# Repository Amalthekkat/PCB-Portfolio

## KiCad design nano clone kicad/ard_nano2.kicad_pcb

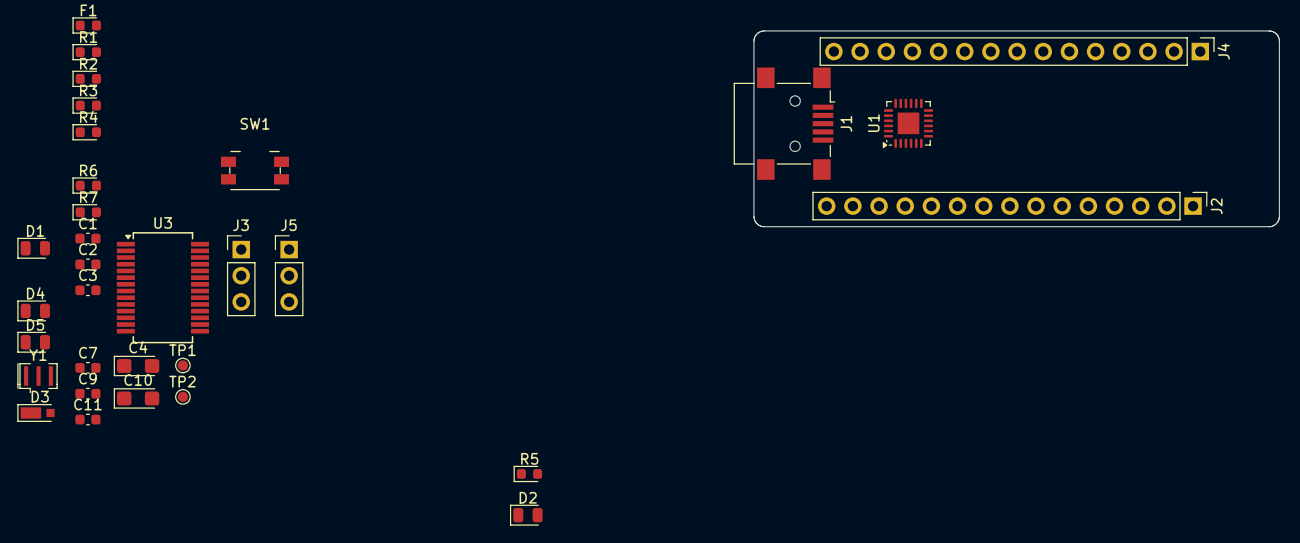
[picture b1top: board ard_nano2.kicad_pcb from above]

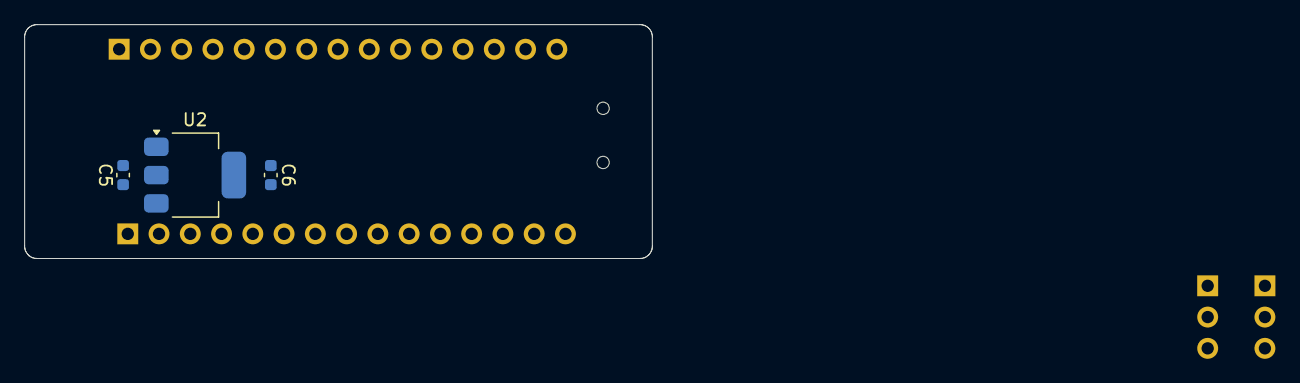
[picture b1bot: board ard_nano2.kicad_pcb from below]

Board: 4 copper layers, 51.0 x 19.0 mm, 35 parts (3 on the bottom side), 40 nets, no tracks yet.

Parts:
C1, C2: 1u; C_0603_1608Metric
C3, C5, C6, C7, C9, C11: 100n; C_0603_1608Metric
C4, C10: 4u7_16V; CP_EIA-3216-10_Kemet-I
D1: YELLOW; LED_0805_2012Metric
D2, D5: GREEN; LED_0805_2012Metric
D3: DIODE; D_MicroSMP_AK
D4: RED; LED_0805_2012Metric
F1: 0603; D_0603_1608Metric
J1: USB_B_Mini; USB_Mini-B_Lumberg_2486_01_Horizontal
J2, J4: PinHeader_1x15_P2.54mm_Vertical
J3: ICSP; PinHeader_1x03_P2.54mm_Vertical
J5: PinHeader_1x03_P2.54mm_Vertical
R1, R2, R3, R4, R5, R6, R7: 1K; D_0603_1608Metric
SW1: Panasonic_EVQPUK_EVQPUB
TP1, TP2: TestPoint_Pad_D1.0mm
U1: ATmega328-M; HVQFN-24-1EP_4x4mm_P0.5mm_EP2.1x2.1mm
U2: LM1117MP-5.0; SOT-223-3_TabPin2
U3: FT232RL; SSOP-28_5.3x10.2mm_P0.65mm
Y1: 16MHz; Resonator_SMD_Murata_CSTxExxV-3Pin_3.0x1.1mm

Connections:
+3V3: C7.1, J2.14, U3.17 (3V3OUT)
+5V: C1.1, C2.1, C4.1, C6.1, D4.2 (A), D5.2 (A), J2.4, J3.1, R1.1, R5.1, U1.4 (VCC), U1.6 (VCC), U1.18 (AVCC), U2.2 (VO), U3.4 (VCCIO), U3.20 (VCC)
/A0: J2.12, U1.23 (PC0)
/A1: J2.11, U1.24 (PC1)
/A2: J2.10, U1.25 (PC2)
/A6: J2.6, U1.19 (ADC6)
/A7: J2.5, U1.22 (ADC7)
/AREF: C3.1, J2.13, U1.20 (AREF)
/D0/RX: J4.2, R2.1
/D1/TX: J4.1, R3.1
/D3: J4.6, U1.1 (PD3)
/D4: J4.7, U1.2 (PD4)
/D5: J4.8, U1.9 (PD5)
/D6: J4.9, U1.10 (PD6)
/D7: J4.10, U1.11 (PD7)
/D8: J4.11, U1.12 (PB0)
/D9: J4.12, U1.13 (PB1)
/D10: J4.13, U1.14 (PB2)
/D11/MOSI: J3.2, J4.14, U1.15 (PB3)
/D12/MIS0: J4.15, J5.1, U1.16 (PB4)
/D13/SCK: J2.15, J5.2, R4.1, U1.17 (PB5)
/D_N: J1.2 (D-), U3.16 (USBD-)
/D_P: J1.3 (D+), TP1.1, U3.15 (USBD+)
/RESET: C9.1, J2.3, J4.3, J5.3, R1.2, SW1.1
/RX: R2.2, U3.1 (TXD)
/TX: R3.2, U3.5 (RXD)
/XTAL1: U1.7 (XTAL1/PB6), Y1.3
/XTAL2: U1.8 (XTAL2/PB7), Y1.1
GND: C1.2, C2.2, C3.2, C4.2, C5.2, C6.2, C7.2, C10.2, C11.1, D1.1 (K), D2.1 (K), J1.5 (GND), J1.6 (Shield), J2.2, J3.3, J4.4, SW1.2, U2.1 (GND), U3.7 (GND), U3.18 (GND), U3.21 (GND), U3.25 (AGND), U3.26 (TEST), Y1.2
unnamed: D1.2 (A), R4.2
unnamed: D2.2 (A), R5.2
unnamed: D4.1 (K), R6.1
unnamed: D5.1 (K), R7.1
unnamed: F1.2, J1.1 (VBUS)
unnamed: U1.3 (GND), U1.5 (GND), U1.21 (GND)
unnamed: R6.2, U3.23 (CBUS0)
unnamed: R7.2, U3.22 (CBUS1)
unnamed: C9.2, U3.3 (RTS)
VBUS: C10.1, C11.2, D3.2 (A), F1.1
VCC: C5.1, D3.1 (K), J2.1, U2.3 (VI)

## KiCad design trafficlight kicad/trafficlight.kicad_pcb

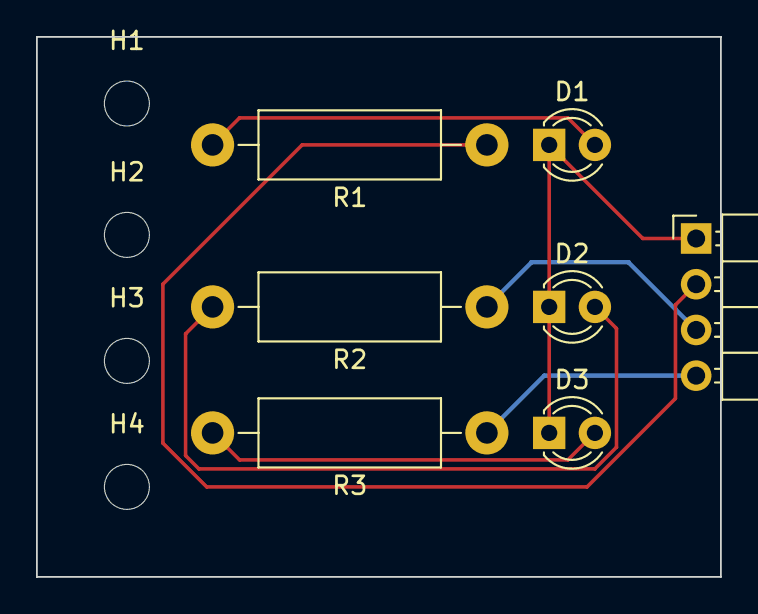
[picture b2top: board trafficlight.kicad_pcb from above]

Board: 2 copper layers, 38.0 x 30.0 mm, 11 parts (0 on the bottom side), 7 nets.

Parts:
D1, D2, D3: LED; LED_D3.0mm_Clear
H1, H2, H3, H4: MountingHole; MountingHole_2.5mm
J1: Conn_01x04_Pin; PinHeader_1x04_P2.54mm_Horizontal
R1, R2, R3: 1k; R_Axial_DIN0411_L9.9mm_D3.6mm_P15.24mm_Horizontal

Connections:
unnamed: D1.2 (A), R1.2
unnamed: D1.1 (K), D2.1 (K), D3.1 (K), J1.1
unnamed: D2.2 (A), R2.2
unnamed: D3.2 (A), R3.2
unnamed: J1.2, R1.1
unnamed: J1.3, R2.1
unnamed: J1.4, R3.1
